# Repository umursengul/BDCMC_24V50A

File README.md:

# BDCMC_24V50A
Dual 24V 50A Brushed DC Motor Controller

This project aims to create an ESC (Electronic Speed Controller) for brushed DC motors wits high power demands. For this purpose an h-bridge and a microcontroller based control board.

A very detailed project that aims to build a 24V 40A brushed DC motor speed controller by Eric Brouwer can be found at https://goo.gl/TH2lnP on Instructables.

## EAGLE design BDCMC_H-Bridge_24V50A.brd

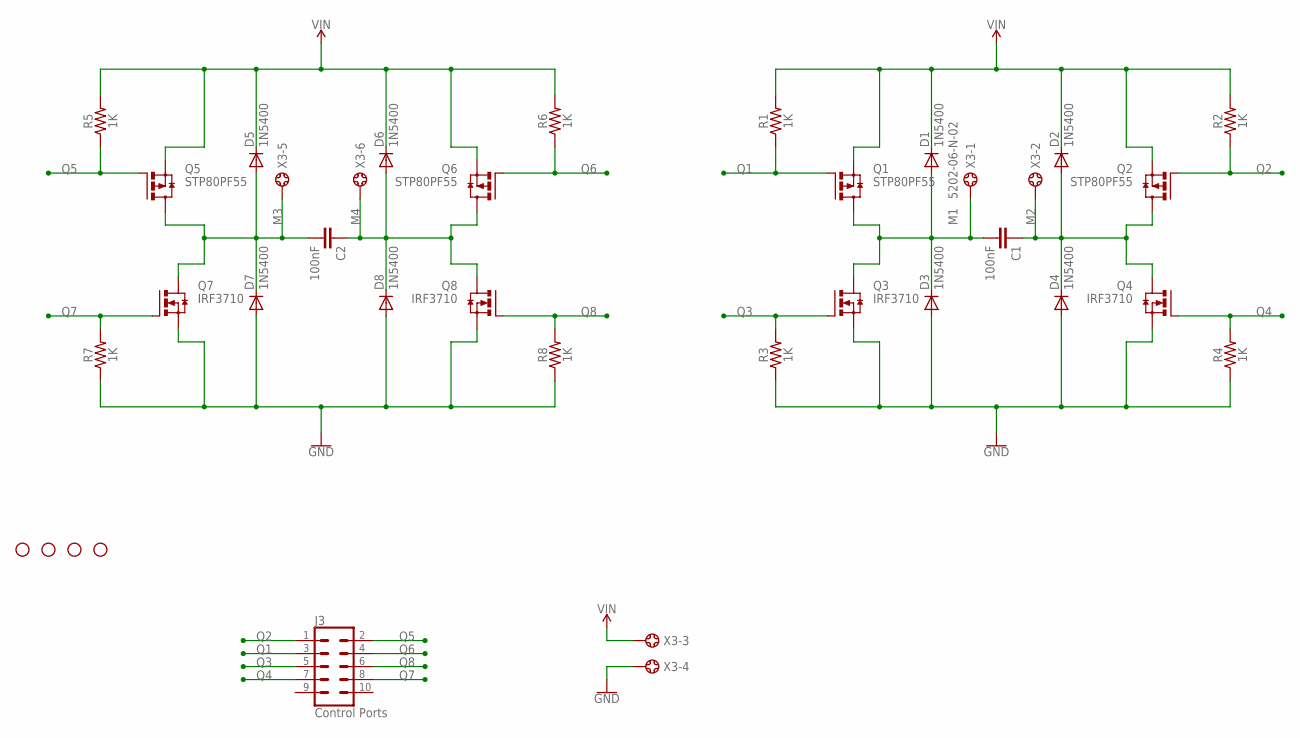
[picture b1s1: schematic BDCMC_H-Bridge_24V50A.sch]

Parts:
C1, C2: 100nF; CAP-PTH-2.54
D1, D2, D3, D4, D5, D6, D7, D8: 1N5400; DO201-15
H1, H2, H3, H4: STAND-OFF
J3: Control Ports; 2X5-SHROUDED
Q1, Q2, Q5, Q6: STP80PF55; TO220
Q3, Q4, Q7, Q8: IRF3710; TO220BH
R1, R2, R3, R4, R5, R6, R7, R8: 1K; AXIAL-0.3
X3: 5202-06-N-02

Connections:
GND: D3.A, D4.A, D7.A, D8.A, Q3.S, Q4.S, Q7.S, Q8.S, R3.P$1 (1), R4.P$1 (1), R7.P$1 (1), R8.P$1 (1), X3.4
M1: C1.2, D1.A, D3.C, Q1.D, Q3.D, X3.1
M2: C1.1, D2.A, D4.C, Q2.D, Q4.D, X3.2
M3: C2.2, D5.A, D7.C, Q5.D, Q7.D, X3.5
M4: C2.1, D6.A, D8.C, Q6.D, Q8.D, X3.6
Q1: J3.3, Q1.G, R1.P$1 (1)
Q2: J3.1, Q2.G, R2.P$1 (1)
Q3: J3.5, Q3.G, R3.P$2 (2)
Q4: J3.7, Q4.G, R4.P$2 (2)
Q5: J3.2, Q5.G, R5.P$1 (1)
Q6: J3.4, Q6.G, R6.P$1 (1)
Q7: J3.8, Q7.G, R7.P$2 (2)
Q8: J3.6, Q8.G, R8.P$2 (2)
VIN: D1.C, D2.C, D5.C, D6.C, Q1.S, Q2.S, Q5.S, Q6.S, R1.P$2 (2), R2.P$2 (2), R5.P$2 (2), R6.P$2 (2), X3.3

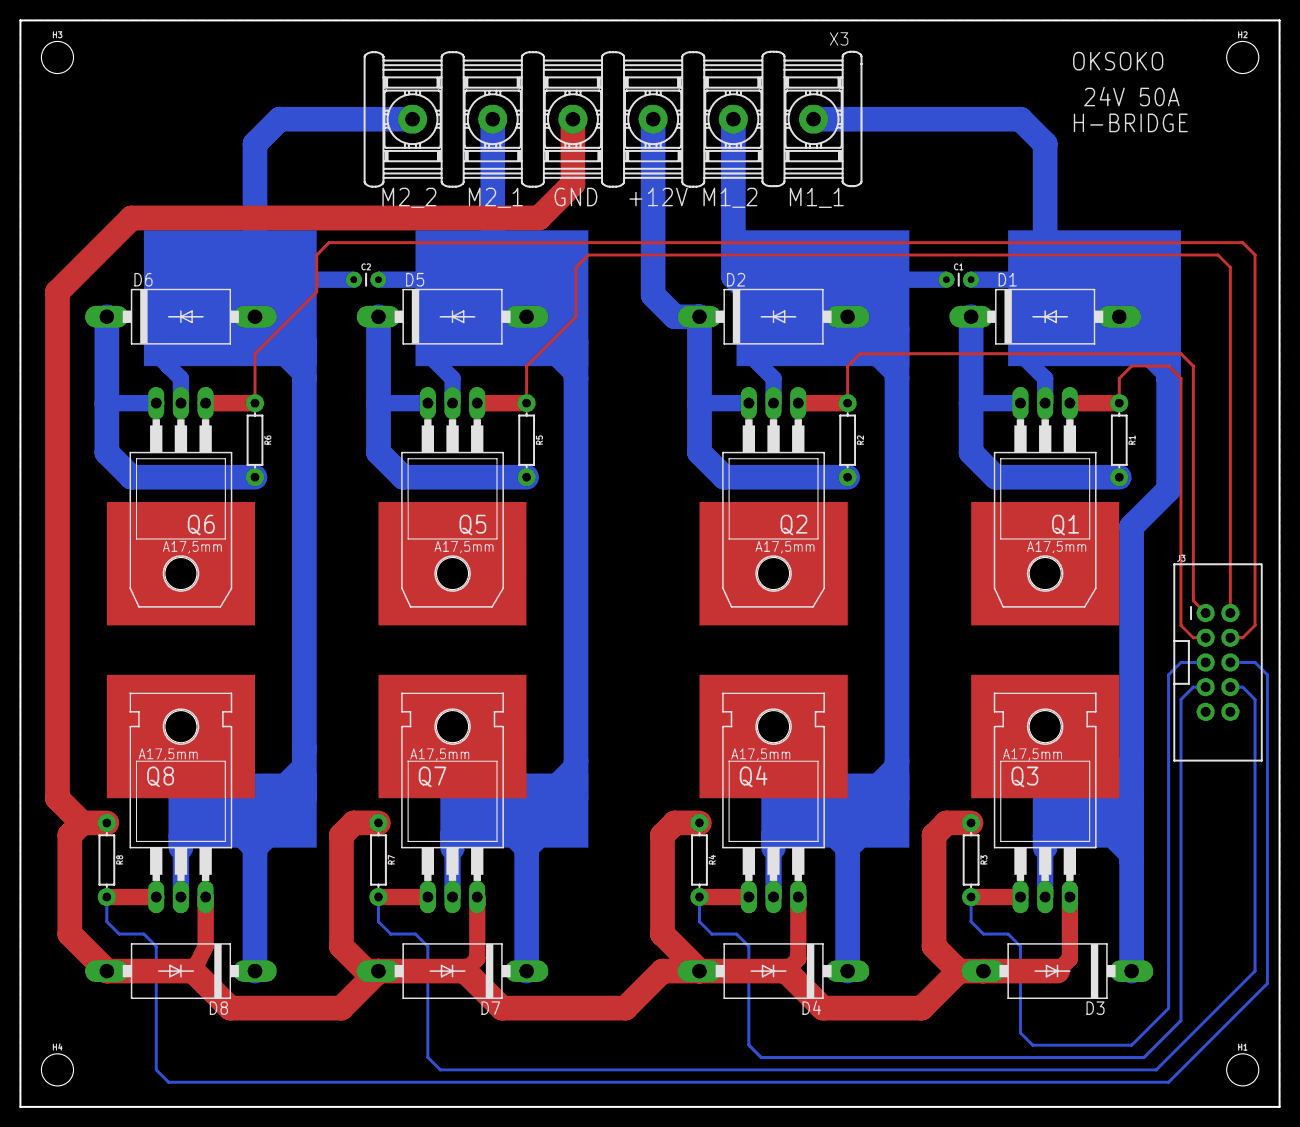
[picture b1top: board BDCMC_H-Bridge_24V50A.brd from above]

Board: 2 copper layers, 129.5 x 111.8 mm, 32 parts (0 on the bottom side), 14 nets.

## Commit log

2017-04-26 H-Bridge design added.
    Brushed DC motor controller dual H-Bridge files design is based on IRF3710 N-Channel HEXFETs and STP80PF55 P-Channel STripFETs with 1N5822 3A Schottky barrier rectifiers as back-EMF protection diodes.
2017-04-26 Eagle "Description" file added.

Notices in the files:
parts and their libraries:
SparkFun_Resistors: Licensing: Creative Commons ShareAlike 4.0 International - https://creativecommons.org/licenses/by-sa/4.0
